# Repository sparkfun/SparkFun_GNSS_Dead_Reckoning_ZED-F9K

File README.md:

SparkFun GNSS-RTK Dead Reckoning Breakout - ZED-F9K (Qwiic)
========================================

[*SparkFun GNSS-RTK Dead Reckoning Breakout - ZED-F9K (Qwiic) (GPS-18719)*](https://www.sparkfun.com/products/18719)

The SparkFun ZED-F9K GNSS Breakout is a high precision, sensor fusion geospatial board with equally impressive configuration options and takes advantage of u-blox's Automotive Dead Reckoning (ADR) technology. The ZED-F9K module provides a highly accurate and continuous position by fusing a 3D IMU sensor, wheel ticks, a vehicle dynamics model, correction data, and GNSS measurements. 

The ZED-F9K module is a 184-channel u-blox F9 engine GNSS receiver, meaning it can receive signals from the GPS, GLONASS, Galileo, and BeiDou constellations with ~0.2 meter accuracy! That's right, such accuracy can be achieved with an  RTK navigation solution when used with a correction source. Note that the ZED-F9K can only operate as a rover, so you will need to connect to a base station. The module supports concurrent reception of four GNSS systems. The combination of GNSS and integrated 3D sensor measurements on the ZED-F9K provide accurate, real-time positioning rates of up to 30Hz.

Compared to other GPS modules, this breakout maximizes position accuracy in dense cities or covered areas. Even under poor signal conditions, continuous positioning is provided in urban environments and is also available during complete signal loss (e.g. short tunnels and parking garages). The ZED-F9K is the ultimate solution for autonomous robotic applications that require accurate positioning under challenging conditions.

Additionally, this u-blox receiver supports I<sup>2</sup>C (u-blox calls this Display Data Channel) which makes it perfect for the Qwiic compatibility so we don't have to use up our precious UART ports. Utilizing our handy Qwiic system, no soldering is required to connect it to the rest of your system. However, we still have broken out 0.1"-spaced pins in case you prefer to use a breadboard.

The SparkFun ZED-F9K GPS Breakout is also equipped with an on-board rechargeable battery that provides power to the RTC on the ZED-F9K.  This reduces the time-to-first fix from a cold start (~26s) to a hot start (~2s). The battery will maintain RTC and GNSS orbit data without being connected to power for plenty of time. The breakout board has five communications ports, four of which are all active simultaneously: USB-C (which enumerates as a COM port), UART1 (with 3.3V TTL), UART2 for RTCM reception (with 3.3V TTL), I<sup>2</sup>C (via the one Qwiic connnector or broken out pins), and SPI. One SMA connector is included for a secure connection to an antenna.

U-blox based GPS products are configurable using the popular, but dense, Windows program called u-center. Plenty of different functions can be configured on the ZED-F9K: baud rates, update rates, geofencing, spoofing detection, external interrupts, SBAS/D-GPS, etc. All of this can be done within the [SparkFun Arduino Library](https://github.com/sparkfun/SparkFun_u-blox_GNSS_Arduino_Library)!

Repository Contents
-------------------

* **/Hardware** - Eagle design files (.brd, .sch)
* **/Production** - Production panel files (.brd)

Documentation
--------------
* **[Library](https://github.com/sparkfun/SparkFun_u-blox_GNSS_Arduino_Library)** - Arduino library
* **[Hookup Guide](https://learn.sparkfun.com/tutorials/2005)** - Basic hookup guide

Product Versions
----------------
* [GPS-18719](https://www.sparkfun.com/products/18719) - Initial release

Version History
---------------
* v1.0 - Initial Release 

License Information
-------------------

This product is _**open source**_! 

Please review the LICENSE.md file for license information. 

If you have any questions or concerns on licensing, please contact technical support on our [SparkFun forums](https://forum.sparkfun.com/viewforum.php?f=152).

Distributed as-is; no warranty is given.

- Your friends at SparkFun.

_<COLLABORATION CREDIT>_

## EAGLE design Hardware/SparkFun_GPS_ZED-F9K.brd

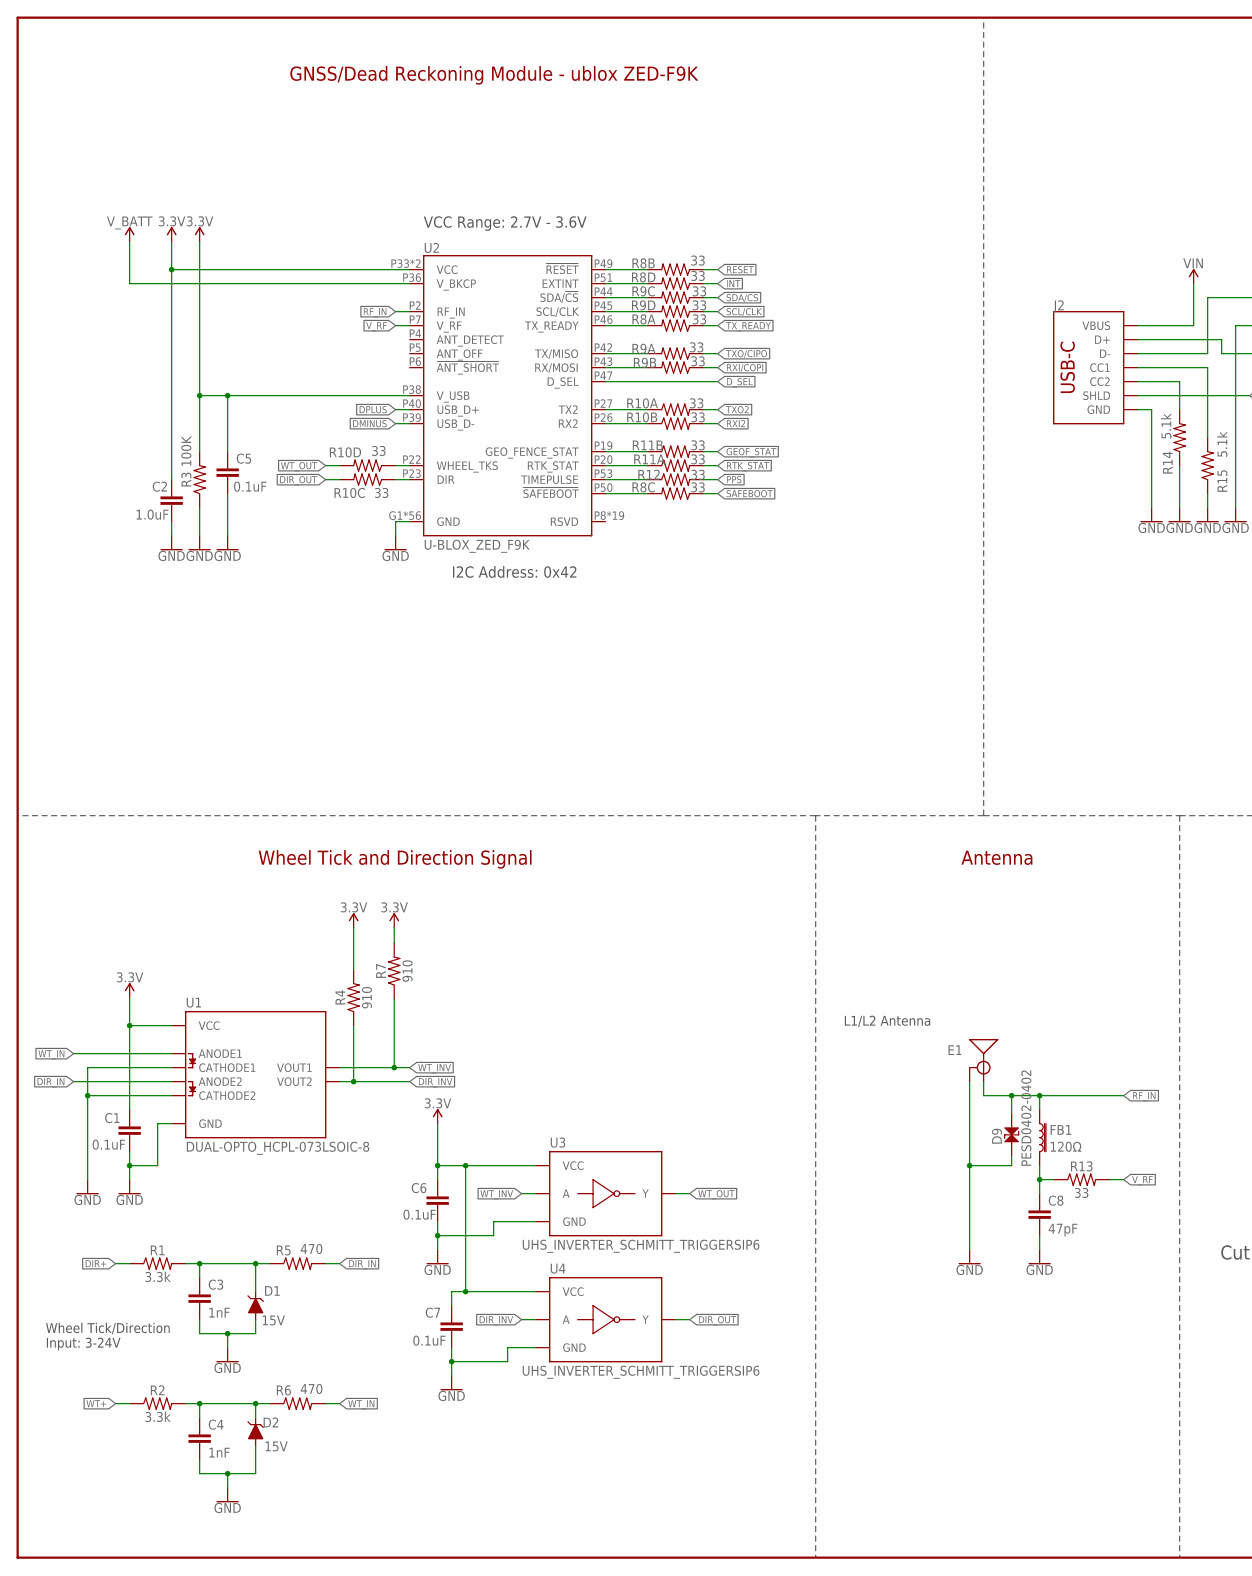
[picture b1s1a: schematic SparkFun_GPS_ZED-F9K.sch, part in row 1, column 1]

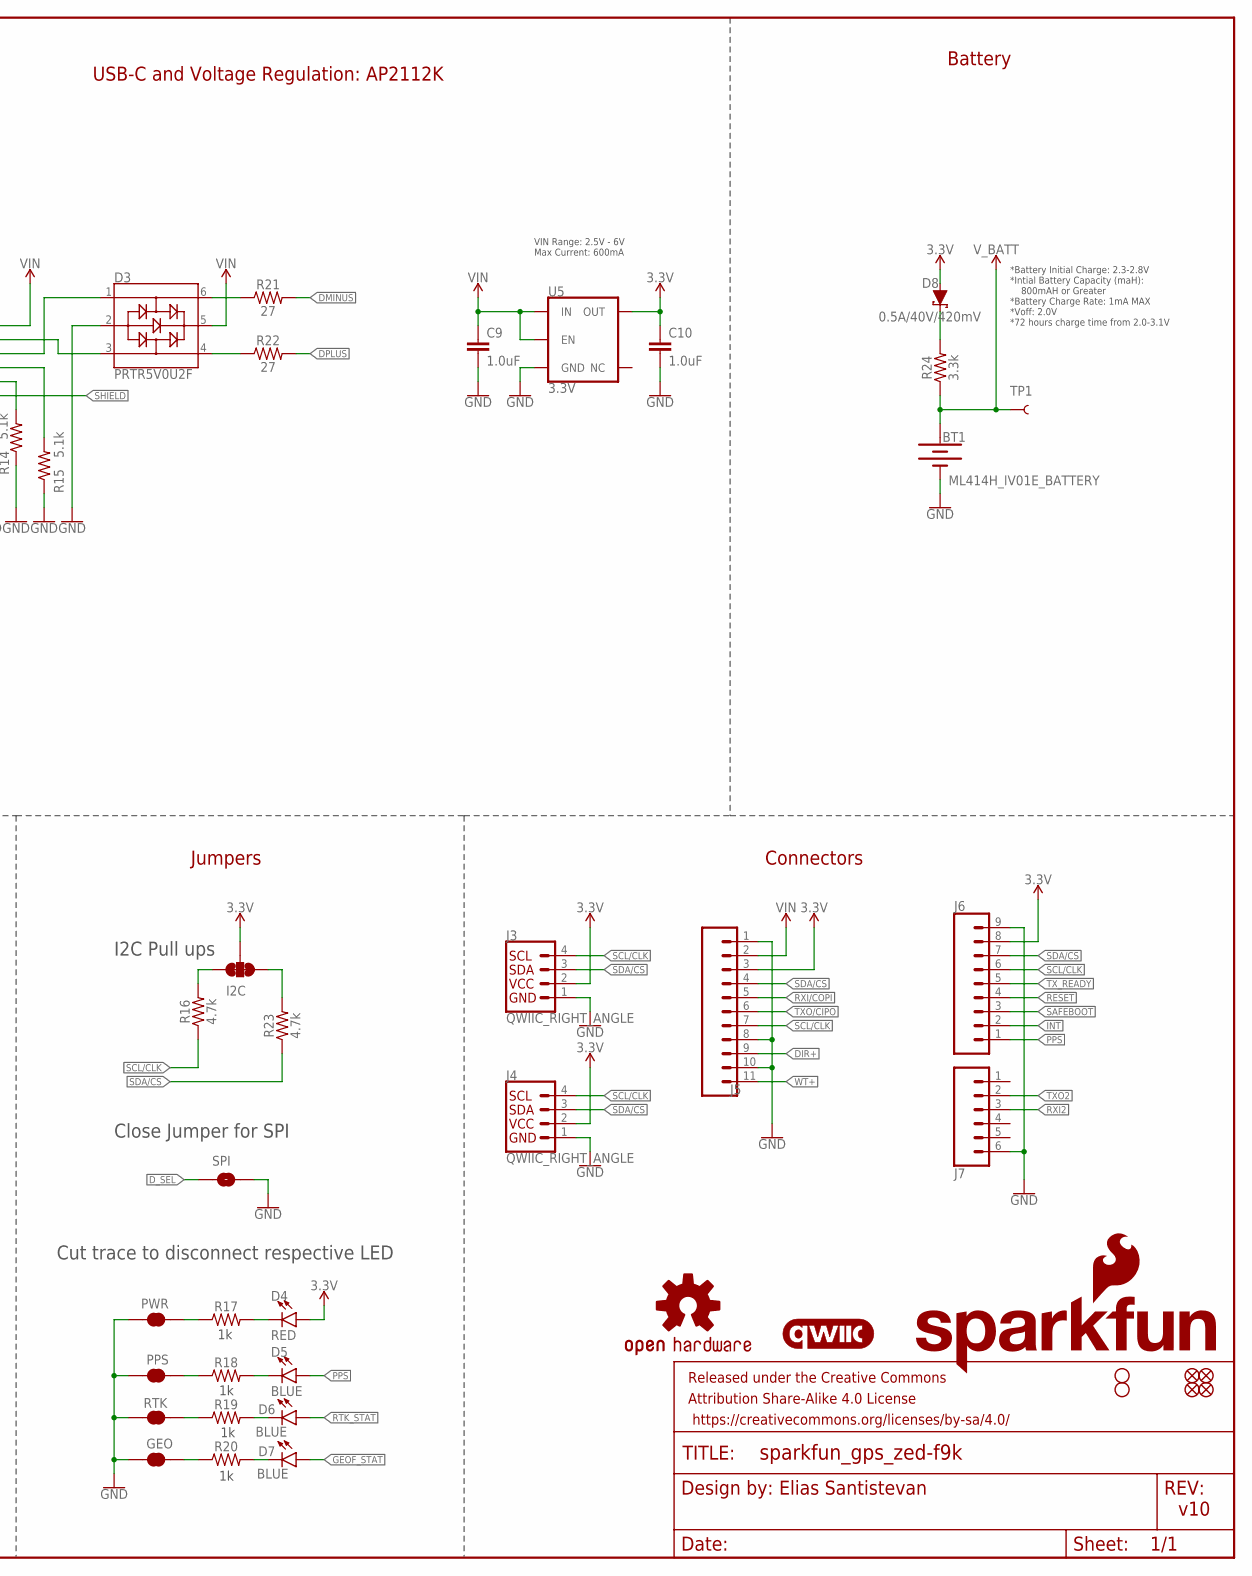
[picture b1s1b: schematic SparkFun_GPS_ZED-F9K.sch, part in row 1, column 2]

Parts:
$1_25_$_2020-03-30_22-52-05: STAND-OFFTIGHT; STAND-OFF-TIGHT
BT1: ML414H_IV01E_BATTERY; ML414H_IV01E
C1, C5, C6, C7: 0.1uF; 0402-TIGHT
C2, C9, C10: 1.0uF; 0402-TIGHT
C3, C4: 1nF; 0402
C8: 47pF; 0402
D1, D2: 15V; SOT23-3
D3: PRTR5V0U2F; SOT886
D4: RED; LED-0603
D5, D6, D7: BLUE; LED-0603
D8: 0.5A/40V/420mV; SOD-323
D9: PESD0402-0402; 0402
E1: ANTENNA-SMA-GROUNDEDEDGE_SMA; SMA-EDGE
FB1: 120Ω; 0402
FD1, FD2, FD3, FD4: FIDUCIALUFIDUCIAL; FIDUCIAL-MICRO
FRAME1: FRAME-LEDGER; CREATIVE_COMMONS
GEO: JUMPER-SMT_2_NC_TRACE_SILK; SMT-JUMPER_2_NC_TRACE_SILK
H2: STAND-OFFTIGHT; STAND-OFF-TIGHT
I2C: JUMPER-SMT_3_2-NC_TRACE_SILK; SMT-JUMPER_3_2-NC_TRACE_SILK
J2: USB_C_2-LAYER_PADS; USB-C-16P-2LAYER-PADS
J3, J4: QWIIC_RIGHT_ANGLE; JST04_1MM_RA
J5: CONN_111X11_NO_SILK; 1X11_NO_SILK
J6: CONN_09NO_SILK; 1X09_NO_SILK
J7: CONN_06NO_SILK_NO_POP; 1X06_NO_SILK
LOGO1: OSHW-LOGOS; OSHW-LOGO-S
LOGO2: QWIIC_LOGO_4MM; QWIIC_4MM
LOGO3: SFE_LOGO_NAME_FLAME.2_INCH; SFE_LOGO_NAME_FLAME_.2
PPS: JUMPER-SMT_2_NC_TRACE_SILK; SMT-JUMPER_2_NC_TRACE_SILK
PWR: JUMPER-SMT_2_NC_TRACE_SILK; SMT-JUMPER_2_NC_TRACE_SILK
R1, R2, R24: 3.3k; 0603
R3: 100K; 0402
R4, R7: 910; 0603
R5, R6: 470; 0603
R8, R9, R10, R11: 33; 1206_RA
R12, R13: 33; 0603
R14, R15: 5.1k; 0402
R16, R23: 4.7k; 0402-TIGHT
R17, R18, R19, R20: 1KOHM-0402-1/16W-1%; 0402
R21, R22: 27; 0603
RTK: JUMPER-SMT_2_NC_TRACE_SILK; SMT-JUMPER_2_NC_TRACE_SILK
SPI: JUMPER-SMT_2_NO_SILK; SMT-JUMPER_2_NO_SILK
TP1: TEST-POINT3X5; PAD.03X.05
U1: DUAL-OPTO_HCPL-073LSOIC-8; SO08
U2: U-BLOX_ZED_F9K; UBLOX_ZED_F9K
U3, U4: UHS_INVERTER_SCHMITT_TRIGGERSIP6; SIP6
U5: 3.3V; SOT23-5

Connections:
3.3V: C1.1, C2.1, C5.1, C6.1, C7.1, C10.1, D4.A, D8.A, I2C.2, J3.2, J4.2, J5.3, J6.8, R3.2, R4.2, R7.2, U1.8 (VCC), U2.P33 (VCC), U2.P34 (VCC), U2.P38 (V_USB), U3.P6 (VCC), U4.P6 (VCC), U5.5 (OUT)
!RESET: J6.4, R8.P2 (1)
!SAFEBOOT: J6.3, R8.P3 (1)
DIR+: J5.9, R1.1
DIR_IN: R5.2, U1.4 (ANODE2)
DIR_INV: R4.1, U1.6 (VOUT2), U4.P2 (A)
DIR_OUT: R10.P6 (2), U4.P4 (Y)
DMINUS: R21.2, U2.P39 (USB_D-)
DPLUS: R22.2, U2.P40 (USB_D+)
D_SEL: SPI.1, U2.P47 (D_SEL)
GEOF_STAT: D7.A, R11.P7 (2)
GND: BT1.-, C1.2, C2.2, C3.2, C4.2, C5.2, C6.2, C7.2, C8.2, C9.2, C10.2, D1.1 (A), D2.1 (A), D3.2, D9.1, E1.GND@0 (GND), E1.GND@1 (GND), E1.GND@2 (GND), E1.GND@3 (GND), GEO.1, J2.GND, J2.GND2 (GND), J3.1, J4.1, J5.1, J5.8, J5.10, J6.9, J7.6, PPS.1, PWR.1, R3.1, R14.1, R15.1, RTK.1, SPI.2, U1.2 (CATHODE1), U1.3 (CATHODE2), U1.5 (GND), U2.G1 (GND), U2.G2 (GND), U2.G3 (GND), U2.G4 (GND), U2.G5 (GND), U2.G6 (GND), U2.G7 (GND), U2.G8 (GND), U2.G9 (GND), U2.G10 (GND), U2.G11 (GND), U2.G12 (GND), U2.G13 (GND), U2.G14 (GND), U2.G15 (GND), U2.G16 (GND), U2.G17 (GND), U2.G18 (GND), U2.G19 (GND), U2.G20 (GND), U2.G21 (GND), U2.G22 (GND), U2.G23 (GND), U2.G24 (GND), U2.G25 (GND), U2.G26 (GND), U2.G27 (GND), U2.G28 (GND), U2.G29 (GND), U2.G30 (GND), U2.G31 (GND), U2.G32 (GND), U2.G33 (GND), U2.G34 (GND), U2.G35 (GND), U2.G36 (GND), U2.G37 (GND), U2.G38 (GND), U2.G39 (GND), U2.G40 (GND), U2.G41 (GND), U2.G42 (GND), U2.G43 (GND), U2.G44 (GND), U2.G45 (GND), U2.G46 (GND), U2.G47 (GND), U2.G48 (GND), U2.P1 (GND), U2.P3 (GND), U2.P12 (GND), U2.P14 (GND), U2.P32 (GND), U2.P37 (GND), U2.P41 (GND), U2.P48 (GND), U3.P3 (GND), U4.P3 (GND), U5.2 (GND)
INT: J6.2, R8.P4 (1)
unnamed: I2C.1, R23.2
unnamed: D8.C, R24.2
unnamed: I2C.3, R16.2
unnamed: D4.C, R17.2
unnamed: C8.1, FB1.2, R13.1
unnamed: D3.3, J2.A6 (D+), J2.B6 (D+)
unnamed: D3.1, J2.A7 (D-), J2.B7 (D-)
unnamed: PWR.2, R17.1
unnamed: D3.6, R21.1
unnamed: D3.4, R22.1
unnamed: R8.P7 (2), U2.P49 (!RESET!)
unnamed: R8.P5 (2), U2.P51 (EXTINT)
unnamed: J2.B5 (CC2), R14.2
unnamed: J2.A5 (CC1), R15.2
unnamed: R9.P6 (2), U2.P44 (SDA/!CS!)
unnamed: R9.P5 (2), U2.P45 (SCL/CLK)
unnamed: R8.P8 (2), U2.P46 (TX_READY)
unnamed: R9.P8 (2), U2.P42 (TX/MISO)
unnamed: R9.P7 (2), U2.P43 (RX/MOSI)
unnamed: R10.P1 (1), U2.P27 (TX2)
unnamed: R19.1, RTK.2
unnamed: PPS.2, R18.1
unnamed: D5.C, R18.2
unnamed: D6.C, R19.2
unnamed: R10.P2 (1), U2.P26 (RX2)
unnamed: R11.P2 (1), U2.P19 (GEO_FENCE_STAT)
unnamed: R11.P1 (1), U2.P20 (RTK_STAT)
unnamed: R12.1, U2.P53 (TIMEPULSE)
unnamed: R8.P6 (2), U2.P50 (!SAFEBOOT!)
unnamed: R10.P4 (1), U2.P22 (WHEEL_TKS)
unnamed: R10.P3 (1), U2.P23 (DIR)
unnamed: GEO.2, R20.1
unnamed: D7.C, R20.2
unnamed: C4.1, D2.3 (C), R2.2, R6.1
unnamed: C3.1, D1.3 (C), R1.2, R5.1
PPS: D5.A, J6.1, R12.2
RF_IN: D9.2, E1.SIG (SIGNAL), FB1.1, U2.P2 (RF_IN)
RTK_STAT: D6.A, R11.P8 (2)
RXI2: J7.3, R10.P7 (2)
RXI/COPI: J5.5, R9.P2 (1)
SCL/CLK: J3.4, J4.4, J5.7, J6.6, R9.P4 (1), R16.1
SDA/!CS: J3.3, J4.3, J5.4, J6.7, R9.P3 (1), R23.1
SHIELD: J2.SHLD1 (SHLD), J2.SHLD2 (SHLD), J2.SHLD3 (SHLD), J2.SHLD4 (SHLD)
TXO2: J7.2, R10.P8 (2)
TXO/CIPO: J5.6, R9.P1 (1)
TX_READY: J6.5, R8.P1 (1)
VIN: C9.1, D3.5, J2.VBUS1 (VBUS), J2.VBUS2 (VBUS), J5.2, U5.1 (IN), U5.3 (EN)
V_BATT: BT1.+, R24.1, TP1.1, U2.P36 (V_BKCP)
V_RF: R13.2, U2.P7 (V_RF)
WT+: J5.11, R2.1
WT_IN: R6.2, U1.1 (ANODE1)
WT_INV: R7.1, U1.7 (VOUT1), U3.P2 (A)
WT_OUT: R10.P5 (2), U3.P4 (Y)

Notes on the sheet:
v10
Elias Santistevan
GNSS/Dead Reckoning Module - ublox ZED-F9K
Battery
Connectors
Jumpers
Close Jumper for SPI
I2C Pull ups
Cut trace to disconnect respective LED
Antenna
*Battery Initial Charge: 2.3-2.8V *Intial Battery Capacity (maH): 800mAH or Greater *Battery Charge Rate: 1mA MAX *Voff: 2.0V *72 hours charge time from 2.0-3.1V
VIN Range: 2.5V - 6V Max Current: 600mA
USB-C and Voltage Regulation: AP2112K
VCC Range: 2.7V - 3.6V
I2C Address: 0x42
Wheel Tick and Direction Signal
Wheel Tick/Direction Input: 3-24V
L1/L2 Antenna

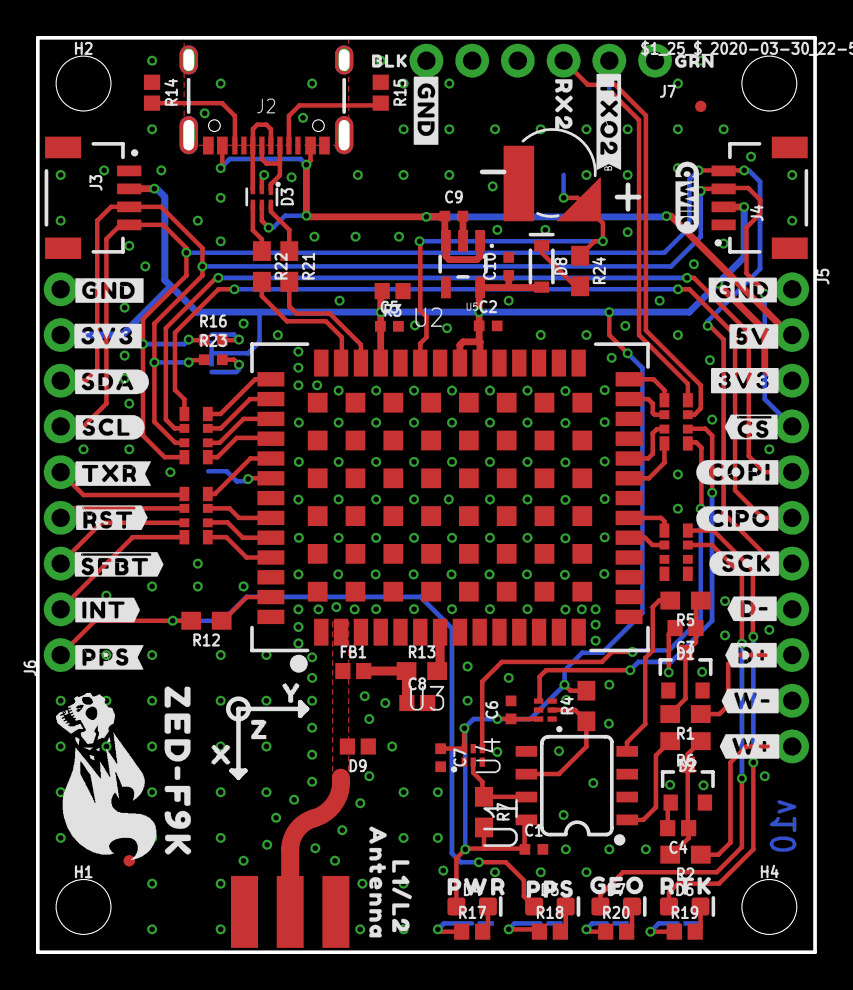
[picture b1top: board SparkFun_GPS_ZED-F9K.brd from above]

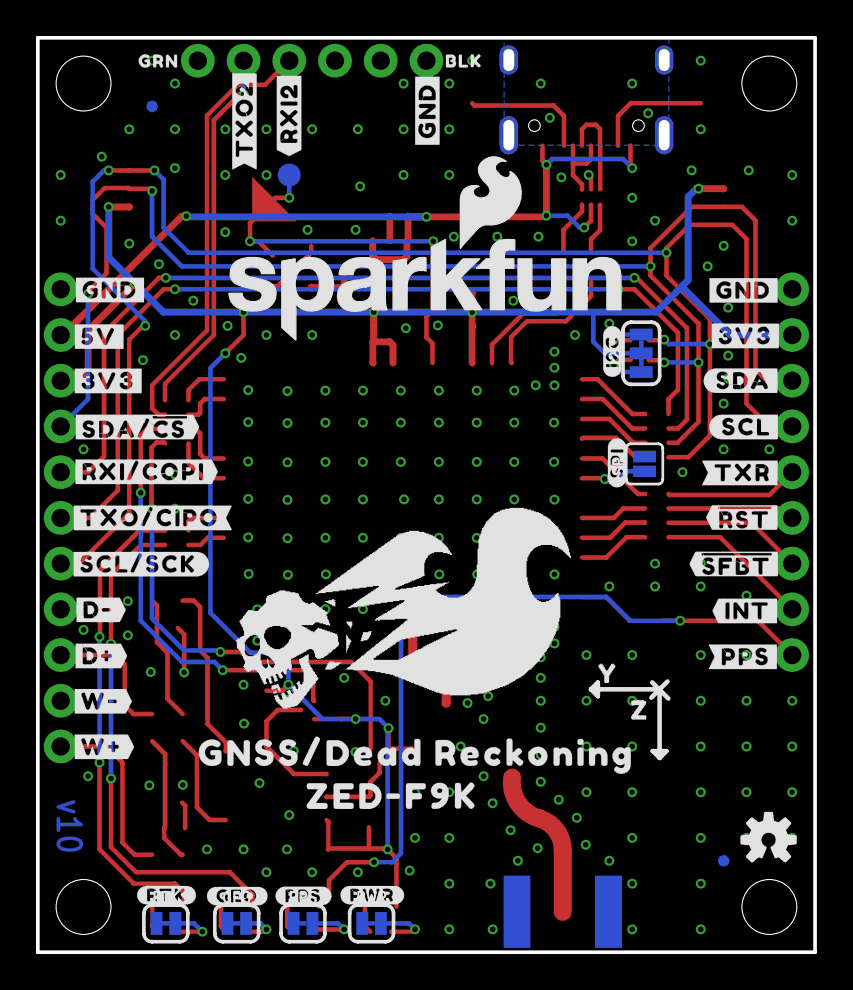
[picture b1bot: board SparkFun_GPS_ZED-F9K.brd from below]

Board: 2 copper layers, 43.2 x 50.8 mm, 149 parts (47 on the bottom side), 66 nets.

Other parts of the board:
H1, H4: STAND-OFFTIGHT; STAND-OFF-TIGHT
U$1: PWR22
U$2: PPS21
U$3: GEO23
U$4: RTK24
U$5: #W##16
U$6: #W##15
U$7, U$14, U$22, U$37, U$55: #3V3#6
U$8: #D##13
U$9: #D##14
U$10: #SCK#12
U$11: #CIPO#10
U$12: #COPI#9
U$13: ##CS##11
U$15, U$24: #5V#1
U$16, U$17, U$25, U$36, U$44, U$58: #GND#0
U$18: #TXO2#20
U$19, U$20: DEAD#RECKONING#GPS#BOARD#SILK#FINAL#JPG
U$21: RX224
U$23: BLK225
U$26: GRN226
U$27: #SDA##CS##10
U$28: #RXI#COPI#8
U$30: #SCL#SCK#12
U$31: #D##6
U$32: X1
U$33: #D##7
U$34: #W##4
U$35: #W##5
U$38: #SDA#6
U$39: #SCL#7
U$40: #TXR#3
U$41: ##RST##16
U$42: ##SFBT##17
U$43: #INT#8
U$45: #PPS#0
U$46: #RTK#25
U$47: #GEO#24
U$48: #PPS#21
U$49: L1#L2229
U$50, U$52: Y2
U$51: #PWR#23
U$53: #SPI#22
U$54: #I2C#23
U$56: #SDA#12
U$57, U$63: Z0
U$59: #RXI2#227
U$60: #TXO2#1
U$61: BLK227
U$62: ANTENNA229
U$64: GRN228
U$65: GNSS#DEAD_RECKONING230
U$66: #SCL#13
U$67: #TXR#19
U$68: ##RST##17
U$69: ##SFBT##18
U$70: #INT#14
U$71: #PPS#20
U$72, U$73: ZED#F9K230
U$74: #TXO#CIPO#9

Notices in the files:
parts and their libraries:
SparkFun-Aesthetics: Licensing: Creative Commons ShareAlike 4.0 International - https://creativecommons.org/licenses/by-sa/4.0
SparkFun-Aesthetics: Released under the Creative Commons Attribution Share-Alike 4.0 License
SparkFun-Aesthetics: https://creativecommons.org/licenses/by-sa/4.0
